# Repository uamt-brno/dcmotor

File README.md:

dcmotor
=======

An driver for DC motor

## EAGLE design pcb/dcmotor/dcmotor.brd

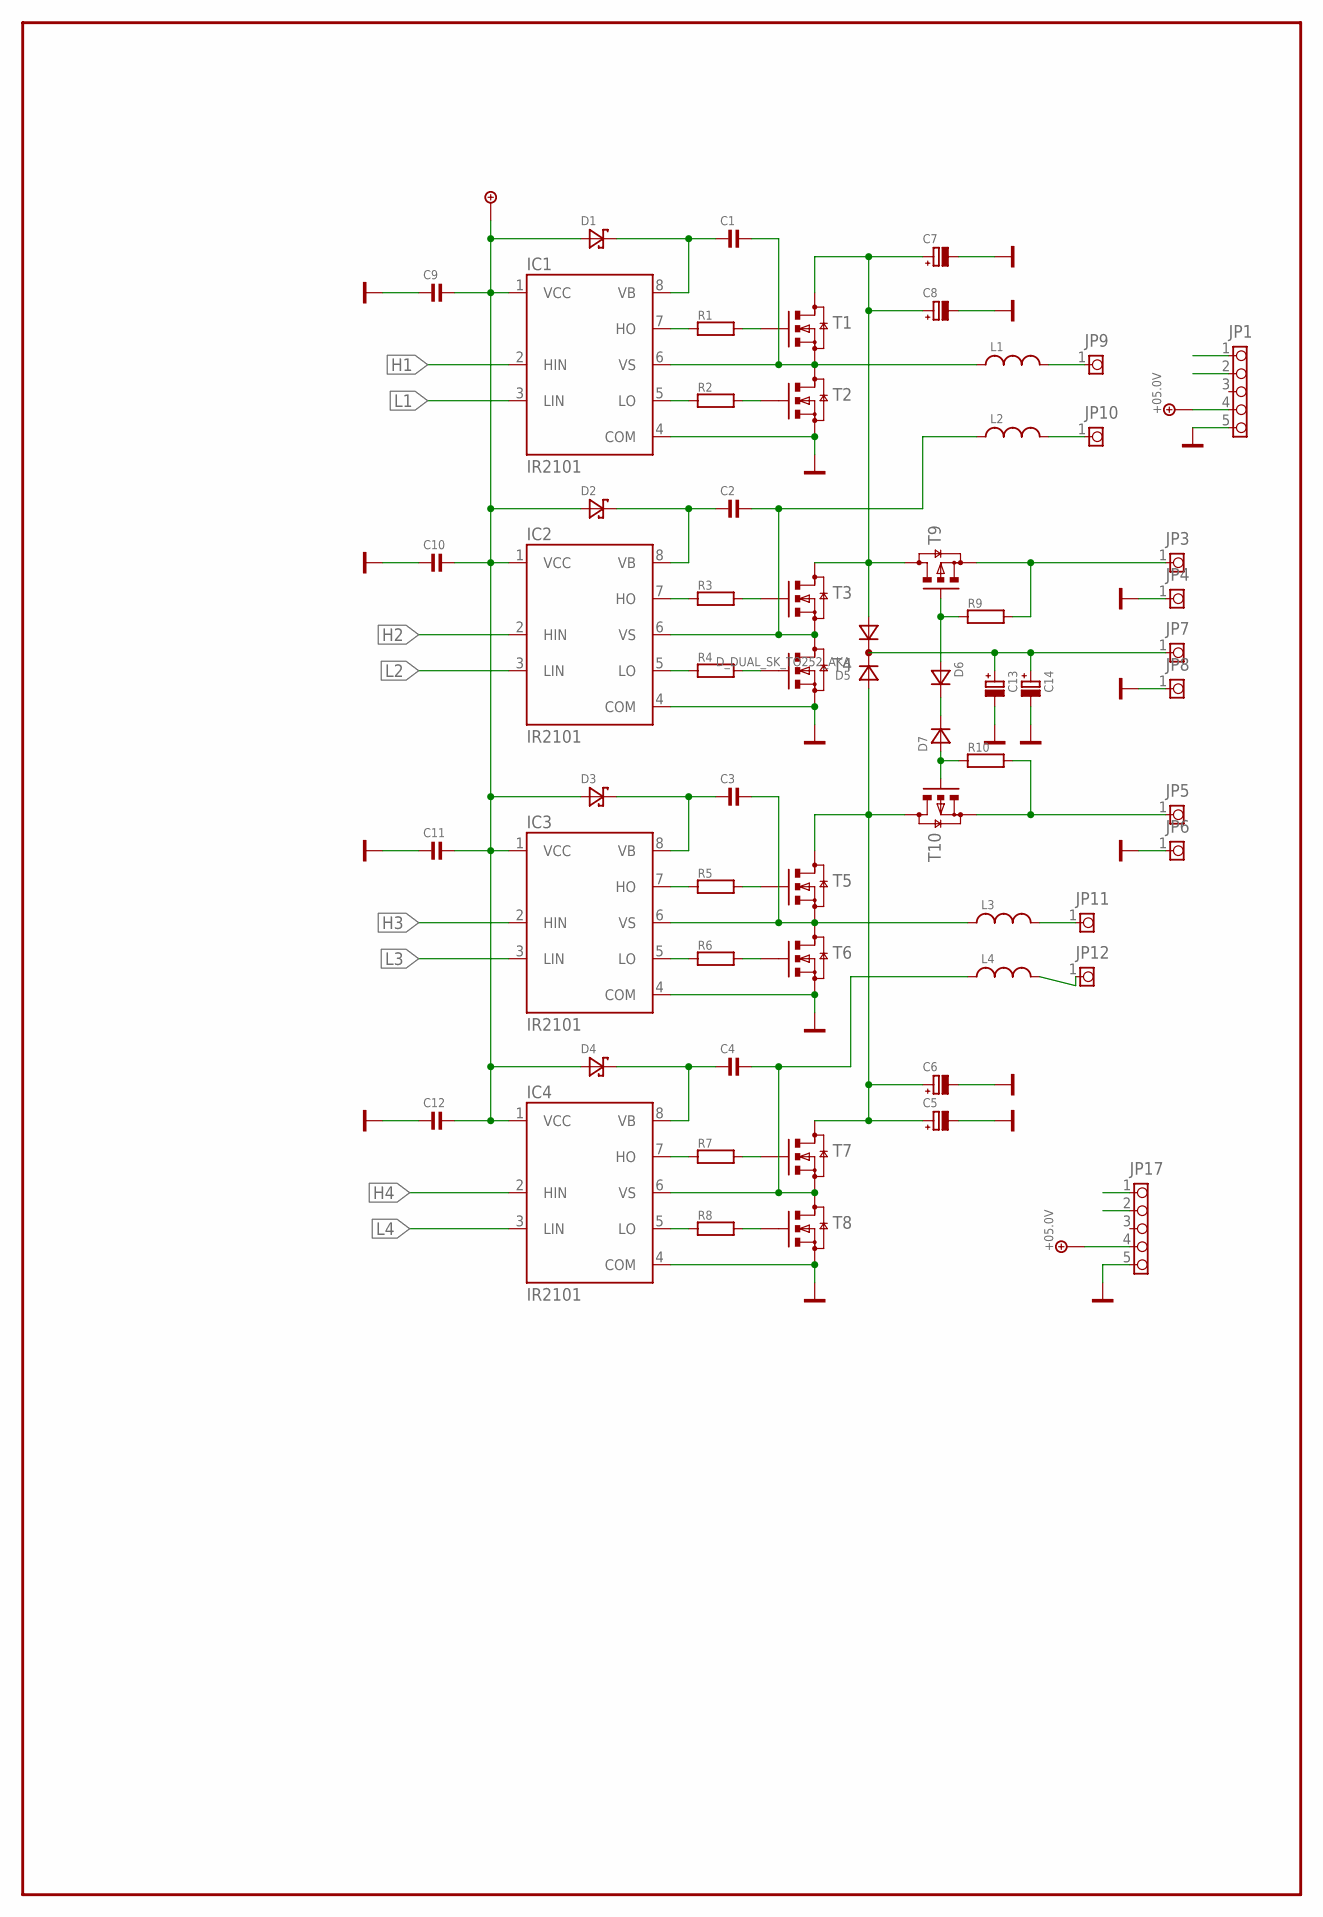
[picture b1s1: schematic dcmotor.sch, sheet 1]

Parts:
C1, C2, C3, C4, C9, C10, C11, C12: C1206; 1206
C5, C6, C7, C8, C13, C14: CECT7343; CT7343D
D1, D2, D3, D4: D_SCHOTKY_MLL34; D_MLL34
D5: D_DUAL_SK_TO252_AKA; TO252
D6, D7: D_MLL34
IC1, IC2, IC3, IC4: IR2101; SO08
JP1, JP17: PINHD-1X5_250_MX5267; 1X05_250_MX5267
JP3, JP4, JP5, JP6, JP7, JP8, JP9, JP10, JP11, JP12: PINHD-1X1; 1X01_254
L1, L2, L3, L4: L_CDRH127
R1, R2, R3, R4, R5, R6, R7, R8, R9, R10: R_R0603; 0603
T1, T2, T3, T4, T5, T6, T7, T8: _EMOS_N_TO252_GDS; TO252
T9, T10: _EMOS_P_TO252_GDS; TO252

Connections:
+5.0V: JP1.4, JP17.4; also elsewhere on the board
+15V: C9.1, C10.1, C11.1, C12.1, D1.A, D2.A, D3.A, D4.A, IC1.1 (VCC), IC2.1 (VCC), IC3.1 (VCC), IC4.1 (VCC)
ENC1A: JP1.1; also elsewhere on the board
ENC1B: JP1.2; also elsewhere on the board
ENC2A: JP17.1; also elsewhere on the board
ENC2B: JP17.2; also elsewhere on the board
GND: C5.-, C6.-, C7.-, C8.-, C9.2, C10.2, C11.2, C12.2, C13.-, C14.-, IC1.4 (COM), IC2.4 (COM), IC3.4 (COM), IC4.4 (COM), JP1.5, JP4.1, JP6.1, JP8.1, JP17.5, T2.3 (S), T4.3 (S), T6.3 (S), T8.3 (S); also elsewhere on the board
H1: IC1.2 (HIN); also elsewhere on the board
H2: IC2.2 (HIN); also elsewhere on the board
H3: IC3.2 (HIN); also elsewhere on the board
H4: IC4.2 (HIN); also elsewhere on the board
L1: IC1.3 (LIN); also elsewhere on the board
L2: IC2.3 (LIN); also elsewhere on the board
L3: IC3.3 (LIN); also elsewhere on the board
L4: IC4.3 (LIN); also elsewhere on the board
unnamed: C1.1, IC1.6 (VS), L1.2, T1.3 (S), T2.2 (D)
unnamed: IC1.7 (HO), R1.1
unnamed: R1.2, T1.1 (G)
unnamed: IC1.5 (LO), R2.1
unnamed: R2.2, T2.1 (G)
unnamed: C7.+, C8.+, D5.1 (A1), T1.2 (D), T3.2 (D), T9.2 (D)
unnamed: C5.+, C6.+, D5.3 (A2), T5.2 (D), T7.2 (D), T10.2 (D)
unnamed: C1.2, D1.K, IC1.8 (VB)
unnamed: C3.1, IC3.6 (VS), L3.2, T5.3 (S), T6.2 (D)
unnamed: C2.1, IC2.6 (VS), L2.2, T3.3 (S), T4.2 (D)
unnamed: IC2.7 (HO), R3.1
unnamed: R3.2, T3.1 (G)
unnamed: IC2.5 (LO), R4.1
unnamed: R4.2, T4.1 (G)
unnamed: IC3.7 (HO), R5.1
unnamed: D6.A, R9.1, T9.1 (G)
unnamed: C2.2, D2.K, IC2.8 (VB)
unnamed: R5.2, T5.1 (G)
unnamed: IC3.5 (LO), R6.1
unnamed: R6.2, T6.1 (G)
unnamed: JP5.1, R10.2, T10.3 (S)
unnamed: C3.2, D3.K, IC3.8 (VB)
unnamed: C4.1, IC4.6 (VS), L4.2, T7.3 (S), T8.2 (D)
unnamed: IC4.7 (HO), R7.1
unnamed: R7.2, T7.1 (G)
unnamed: IC4.5 (LO), R8.1
unnamed: R8.2, T8.1 (G)
unnamed: C13.+, C14.+, D5.2 (K), JP7.1
unnamed: C4.2, D4.K, IC4.8 (VB)
unnamed: JP3.1, R9.2, T9.3 (S)
unnamed: JP11.1, L3.1
unnamed: JP12.1, L4.1
unnamed: JP9.1, L1.1
unnamed: JP10.1, L2.1
unnamed: D7.A, R10.1, T10.1 (G)
unnamed: D6.K, D7.K

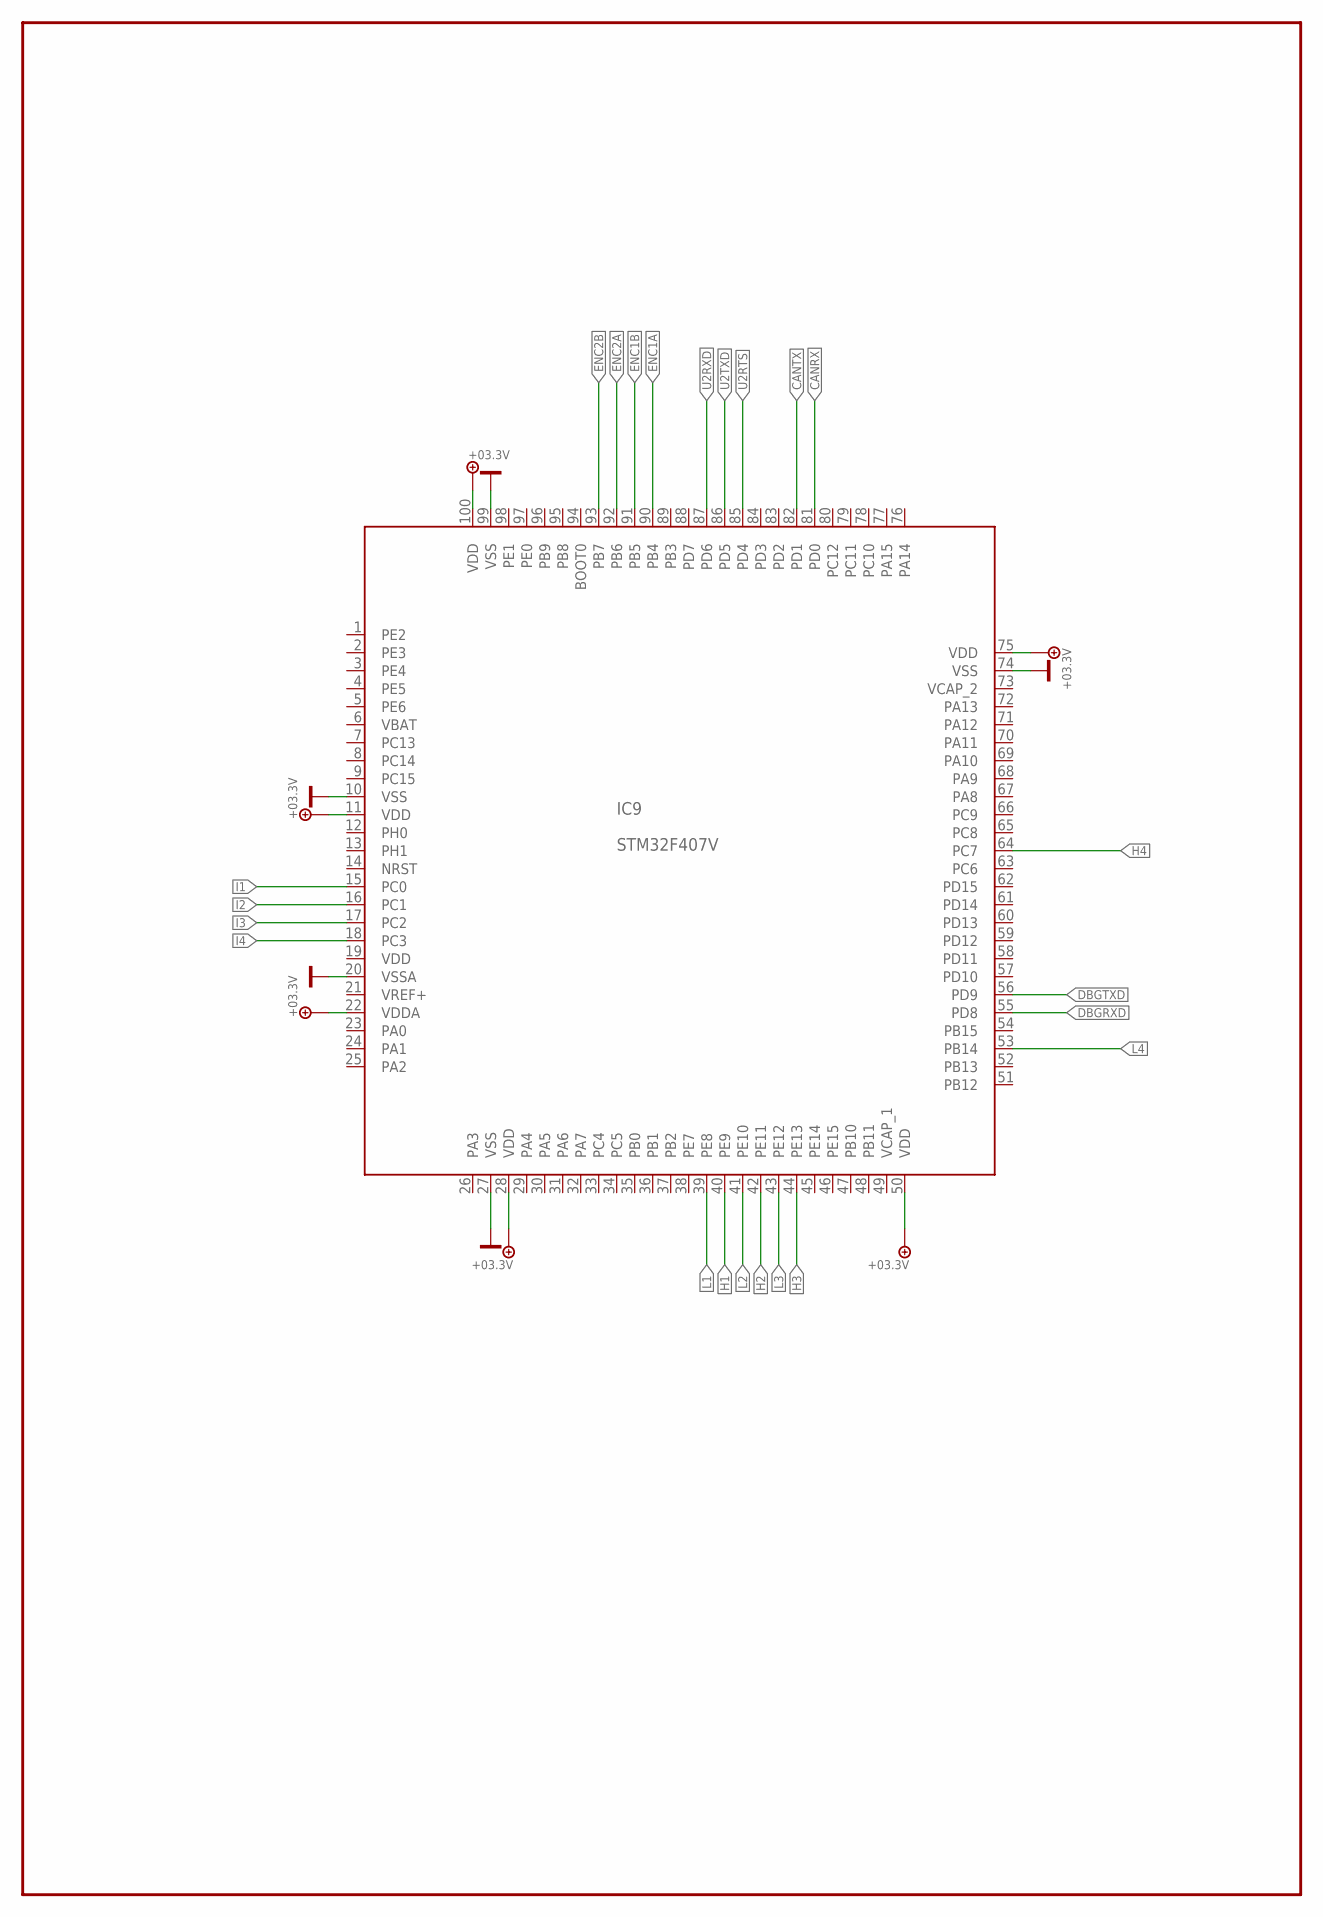
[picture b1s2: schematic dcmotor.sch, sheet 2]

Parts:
IC9: STM32F407V; LQFP100

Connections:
+3.3V: IC9.11 (VDD), IC9.22 (VDDA), IC9.28 (VDD), IC9.50 (VDD), IC9.75 (VDD), IC9.100 (VDD)
CANRX: IC9.81 (PD0); also elsewhere on the board
CANTX: IC9.82 (PD1); also elsewhere on the board
DBGRXD: IC9.55 (PD8)
DBGTXD: IC9.56 (PD9)
ENC1A: IC9.90 (PB4); also elsewhere on the board
ENC1B: IC9.91 (PB5); also elsewhere on the board
ENC2A: IC9.92 (PB6); also elsewhere on the board
ENC2B: IC9.93 (PB7); also elsewhere on the board
GND: IC9.10 (VSS), IC9.20 (VSSA), IC9.27 (VSS), IC9.74 (VSS), IC9.99 (VSS); also elsewhere on the board
H1: IC9.40 (PE9); also elsewhere on the board
H2: IC9.42 (PE11); also elsewhere on the board
H3: IC9.44 (PE13); also elsewhere on the board
H4: IC9.64 (PC7); also elsewhere on the board
I1: IC9.15 (PC0)
I2: IC9.16 (PC1)
I3: IC9.17 (PC2)
I4: IC9.18 (PC3)
L1: IC9.39 (PE8); also elsewhere on the board
L2: IC9.41 (PE10); also elsewhere on the board
L3: IC9.43 (PE12); also elsewhere on the board
L4: IC9.53 (PB14); also elsewhere on the board
U2RTS: IC9.85 (PD4); also elsewhere on the board
U2RXD: IC9.87 (PD6); also elsewhere on the board
U2TXD: IC9.86 (PD5); also elsewhere on the board

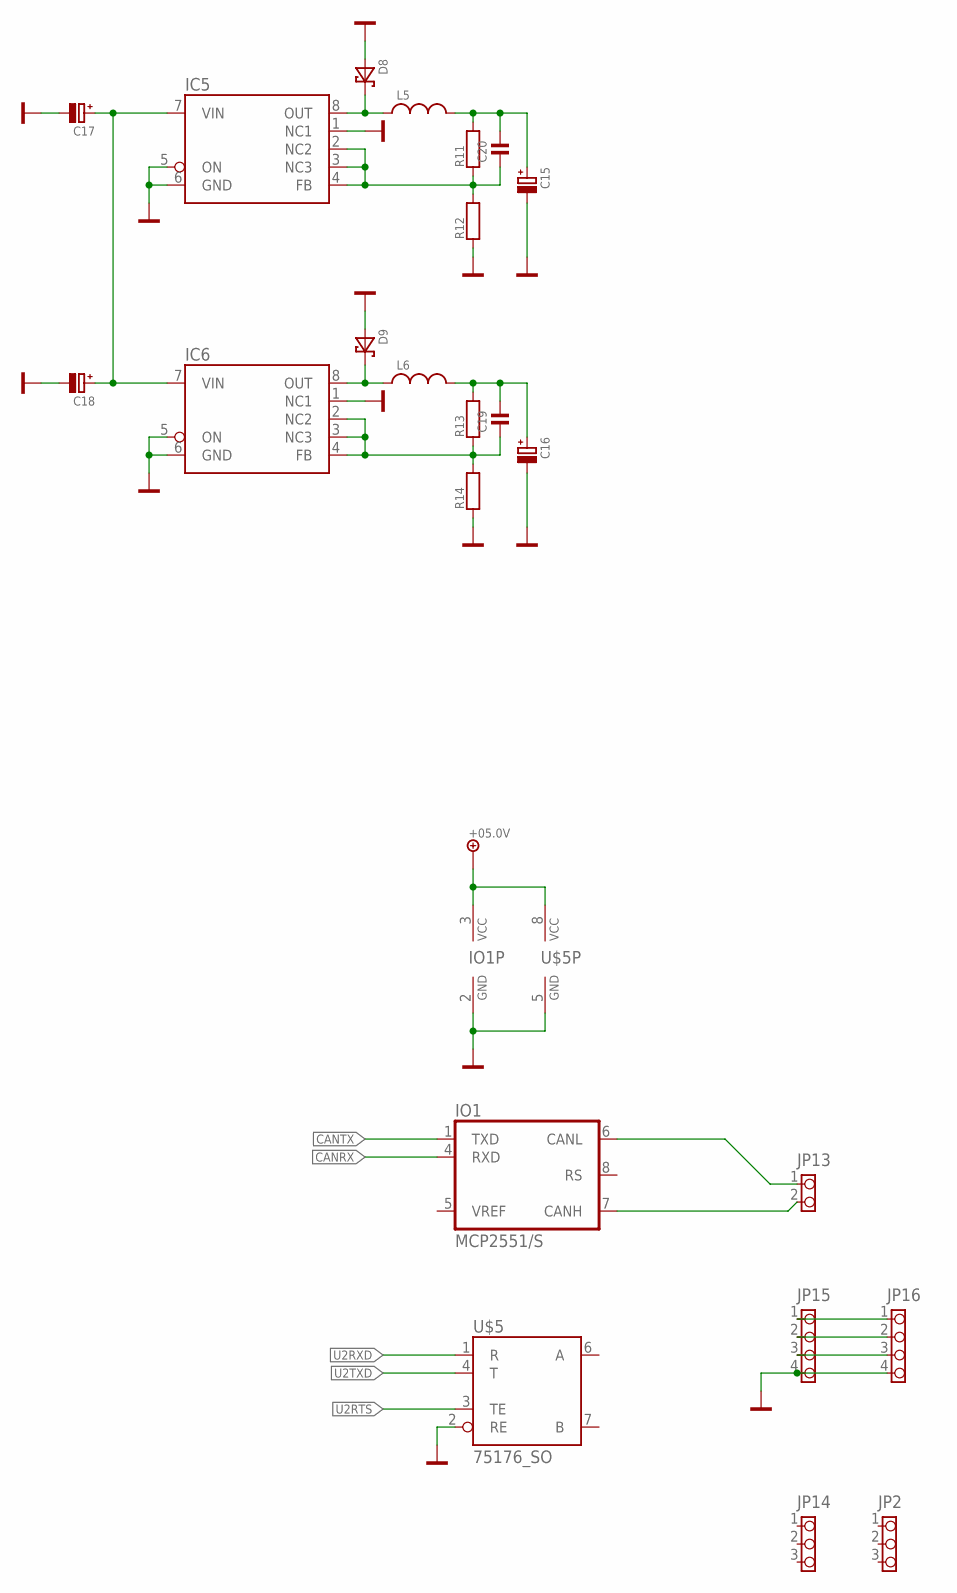
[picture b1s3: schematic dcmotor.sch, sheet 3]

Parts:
C15, C16, C17, C18: CECT7343; CT7343D
C19, C20: C0603; 0603
D8, D9: D_SCHOTKY_SMB; D_SMB
IC5, IC6: LM2594_SO; SO08
IO1: MCP2551/S; SO08
JP2, JP14: PINHD-1X3_250_MX5267; 1X03_250_MX5267
JP13: PINHD-1X2_250_MX5267; 1X02_250_MX5267
JP15, JP16: PINHD-1X4_250_MX5267; 1X04_250_MX5267
L5, L6: L_SMD_350_200; L_350_200
R11, R12, R13, R14: R_R0603; 0603
U$5: 75176_SO; SO08

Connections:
+5.0V: IO1.3 (VCC), U$5.8 (VCC); also elsewhere on the board
CANRX: IO1.4 (RXD); also elsewhere on the board
CANTX: IO1.1 (TXD); also elsewhere on the board
GND: C15.-, C16.-, C17.-, C18.-, D8.A, D9.A, IC5.1 (NC1), IC5.5 (ON), IC5.6 (GND), IC6.1 (NC1), IC6.5 (ON), IC6.6 (GND), IO1.2 (GND), JP15.4, JP16.4, R12.1, R14.1, U$5.2 (RE), U$5.5 (GND); also elsewhere on the board
unnamed: JP15.1, JP16.1
unnamed: JP15.2, JP16.2
unnamed: JP15.3, JP16.3
unnamed: D8.K, IC5.8 (OUT), L5.2
unnamed: IO1.6 (CANL), JP13.1
unnamed: IO1.7 (CANH), JP13.2
unnamed: D9.K, IC6.8 (OUT), L6.2
unnamed: C16.+, C19.1, L6.1, R13.2
unnamed: C15.+, C20.1, L5.1, R11.2
unnamed: C20.2, IC5.2 (NC2), IC5.3 (NC3), IC5.4 (FB), R11.1, R12.2
unnamed: C19.2, IC6.2 (NC2), IC6.3 (NC3), IC6.4 (FB), R13.1, R14.2
unnamed: C17.+, C18.+, IC5.7 (VIN), IC6.7 (VIN)
U2RTS: U$5.3 (TE); also elsewhere on the board
U2RXD: U$5.1 (R); also elsewhere on the board
U2TXD: U$5.4 (T); also elsewhere on the board

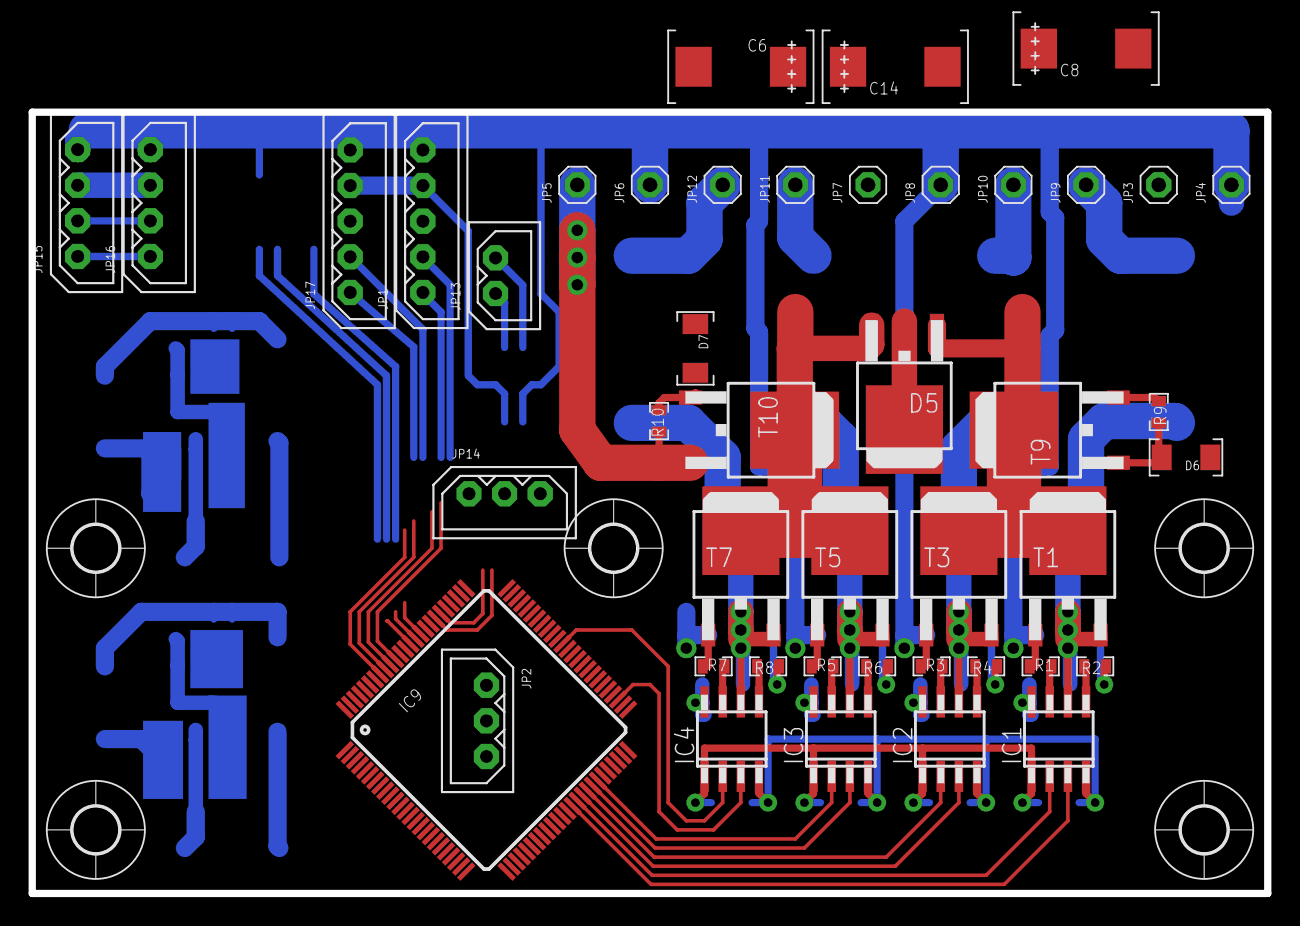
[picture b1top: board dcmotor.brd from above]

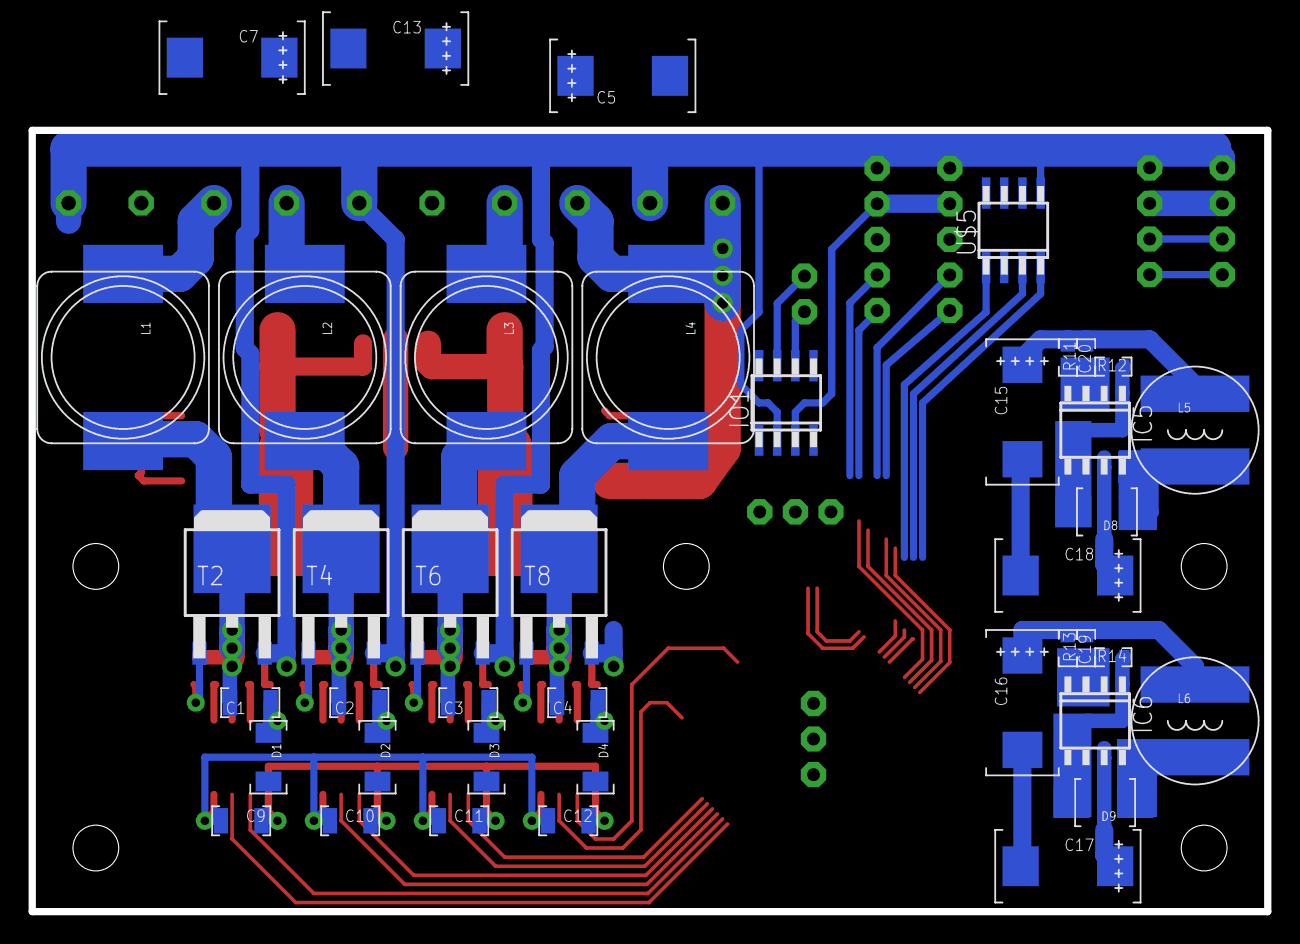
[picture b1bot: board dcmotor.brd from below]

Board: 2 copper layers, 86.4 x 54.6 mm, 90 parts (41 on the bottom side), 69 nets.

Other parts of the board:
U$1, U$2, U$3, U$4, U$6: 3,2

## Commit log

2013-09-21 [PCB] Add preliminary board and schematics
2014-03-10 novy fw
2014-03-10 pridam projekt
2014-03-24 blikanie dvoma ledkami
